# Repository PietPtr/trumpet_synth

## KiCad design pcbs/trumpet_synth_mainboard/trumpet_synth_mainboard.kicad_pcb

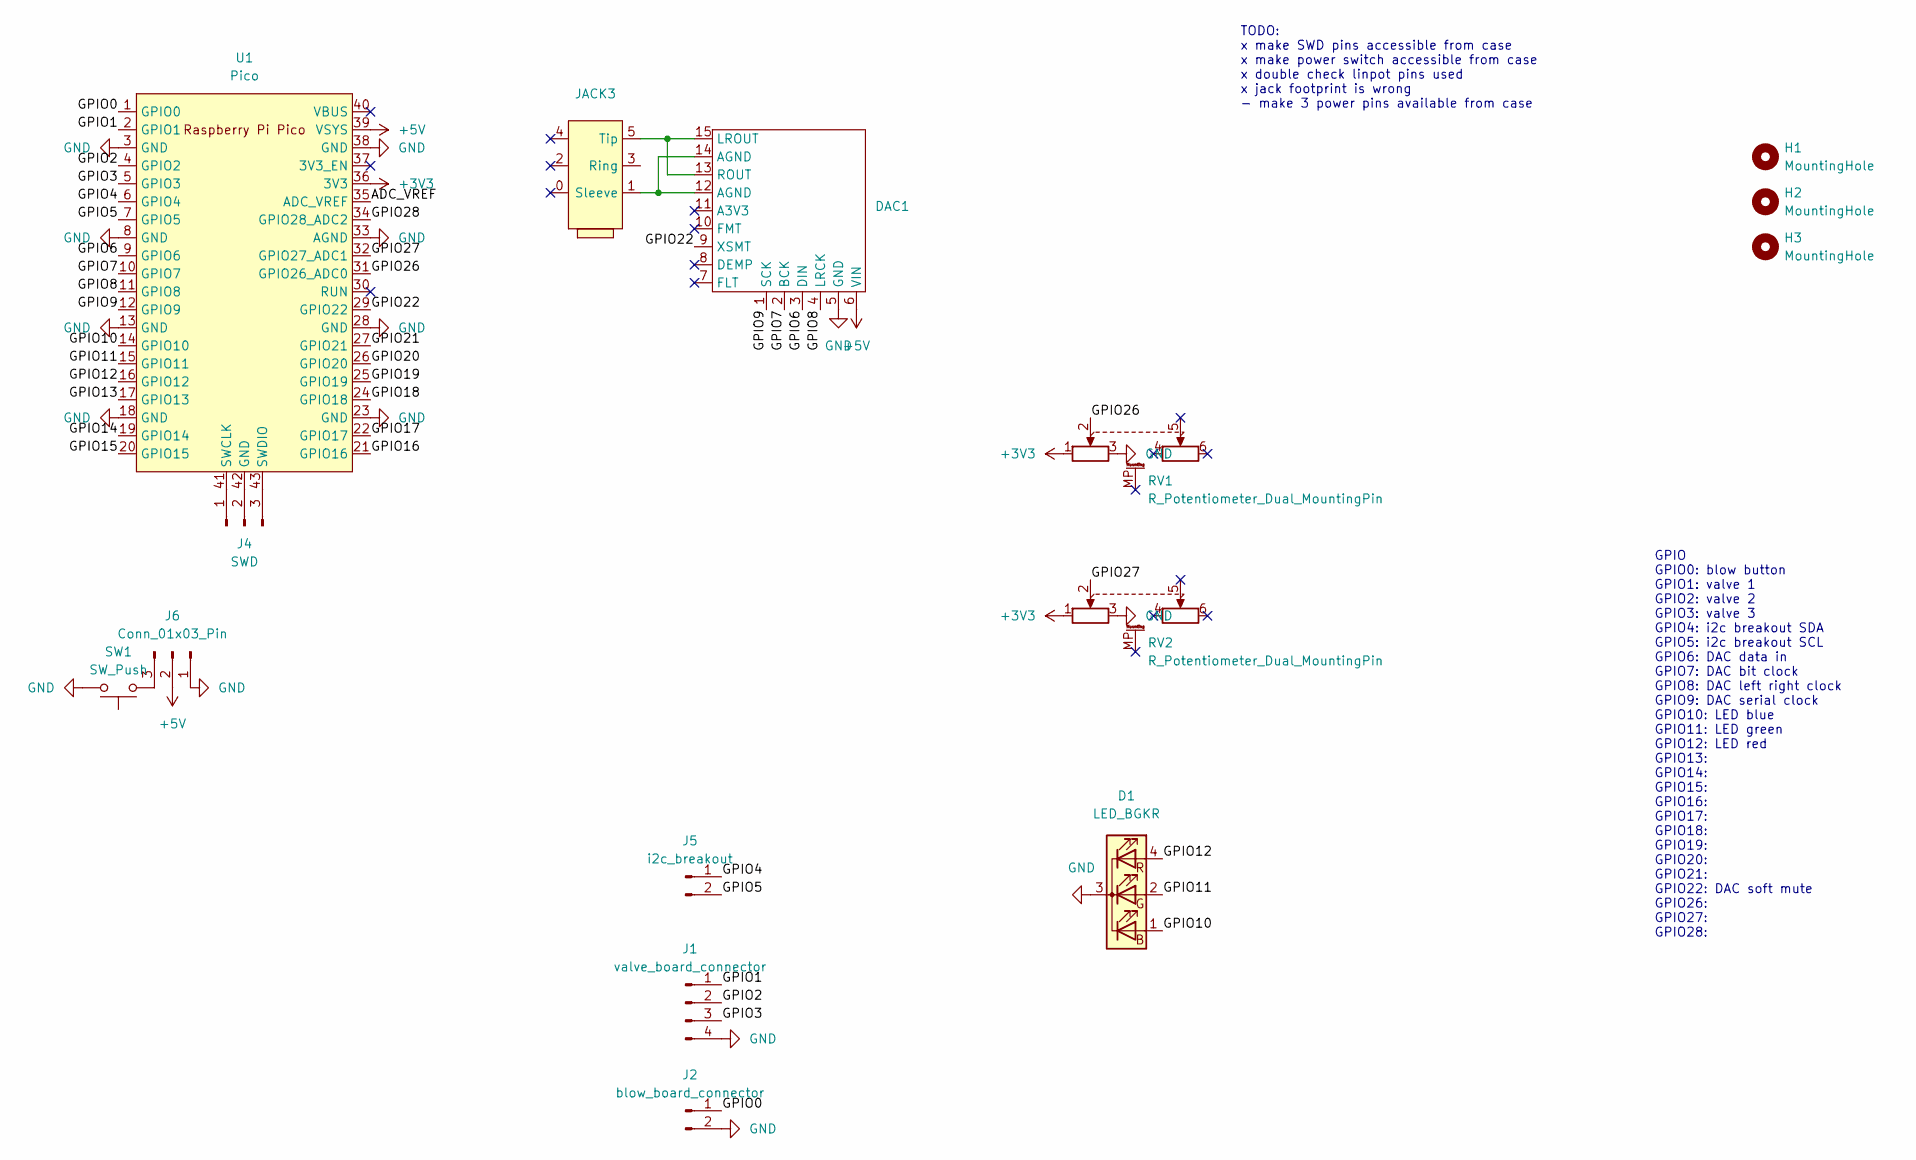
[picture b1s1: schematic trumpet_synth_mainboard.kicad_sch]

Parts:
D1: LED_BGKR; LED_D5.0mm-4_RGB
DAC1: PCM5102_BREAKOUT
H1, H2, H3: MountingHole; MountingHole_3.2mm_M3
J1: valve_board_connector; PinHeader_1x04_P2.54mm_Vertical
J2: blow_board_connector; PinHeader_1x02_P2.54mm_Vertical
J4: SWD; PinHeader_1x03_P2.54mm_Vertical
J5: i2c_breakout; PinHeader_1x02_P2.54mm_Vertical
J6: Conn_01x03_Pin; PinHeader_1x03_P2.54mm_Vertical
JACK3: SlimJack6.3
RV1, RV2: R_Potentiometer_Dual_MountingPin; linpot_75mm
SW1: SW_Push; PinHeader_1x03_P2.54mm_Vertical
U1: Pico; RPi_Pico_SMD

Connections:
+3V3: RV1.1, RV2.1, U1.36 (3V3)
+5V: DAC1.6 (VIN), J6.2, U1.39 (VSYS)
/ADC_VREF: U1.35 (ADC_VREF)
/GPIO0: J2.1, U1.1 (GPIO0)
/GPIO1: J1.1, U1.2 (GPIO1)
/GPIO2: J1.2, U1.4 (GPIO2)
/GPIO3: J1.3, U1.5 (GPIO3)
/GPIO4: J5.1, U1.6 (GPIO4)
/GPIO5: J5.2, U1.7 (GPIO5)
/GPIO6: DAC1.3 (DIN), U1.9 (GPIO6)
/GPIO7: DAC1.2 (BCK), U1.10 (GPIO7)
/GPIO8: DAC1.4 (LRCK), U1.11 (GPIO8)
/GPIO9: DAC1.1 (SCK), U1.12 (GPIO9)
/GPIO10: D1.1 (BA), U1.14 (GPIO10)
/GPIO11: D1.2 (GA), U1.15 (GPIO11)
/GPIO12: D1.4 (RA), U1.16 (GPIO12)
/GPIO13: U1.17 (GPIO13)
/GPIO14: U1.19 (GPIO14)
/GPIO15: U1.20 (GPIO15)
/GPIO16: U1.21 (GPIO16)
/GPIO17: U1.22 (GPIO17)
/GPIO18: U1.24 (GPIO18)
/GPIO19: U1.25 (GPIO19)
/GPIO20: U1.26 (GPIO20)
/GPIO21: U1.27 (GPIO21)
/GPIO22: DAC1.9 (XSMT), U1.29 (GPIO22)
/GPIO26: RV1.2, U1.31 (GPIO26_ADC0)
/GPIO27: RV2.2, U1.32 (GPIO27_ADC1)
/GPIO28: U1.34 (GPIO28_ADC2)
GND: D1.3 (K), DAC1.5 (GND), J1.4, J2.2, J6.1, RV1.3, RV2.3, SW1.2, U1.3 (GND), U1.8 (GND), U1.13 (GND), U1.18 (GND), U1.23 (GND), U1.28 (GND), U1.33 (AGND), U1.38 (GND)
unnamed: DAC1.13 (ROUT), DAC1.15 (LROUT), JACK3.5 (Tip)
unnamed: J4.1, U1.41 (SWCLK)
unnamed: J4.2, U1.42 (GND)
unnamed: J4.3, U1.43 (SWDIO)
unnamed: J6.3, SW1.1
unnamed: DAC1.12 (AGND), DAC1.14 (AGND), JACK3.1 (Sleeve)

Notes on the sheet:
TODO: x make SWD pins accessible from case x make power switch accessible from case x double check linpot pins used x jack footprint is wrong - make 3 power pins available from case
GPIO GPIO0: blow button GPIO1: valve 1 GPIO2: valve 2 GPIO3: valve 3 GPIO4: i2c breakout SDA GPIO5: i2c breakout SCL GPIO6: DAC data in GPIO7: DAC bit clock GPIO8: DAC left right clock GPIO9: DAC serial clock GPIO10: LED blue GPIO11: LED green GPIO12: LED red GPIO13: GPIO14: GPIO15: GPIO16: GPIO17: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

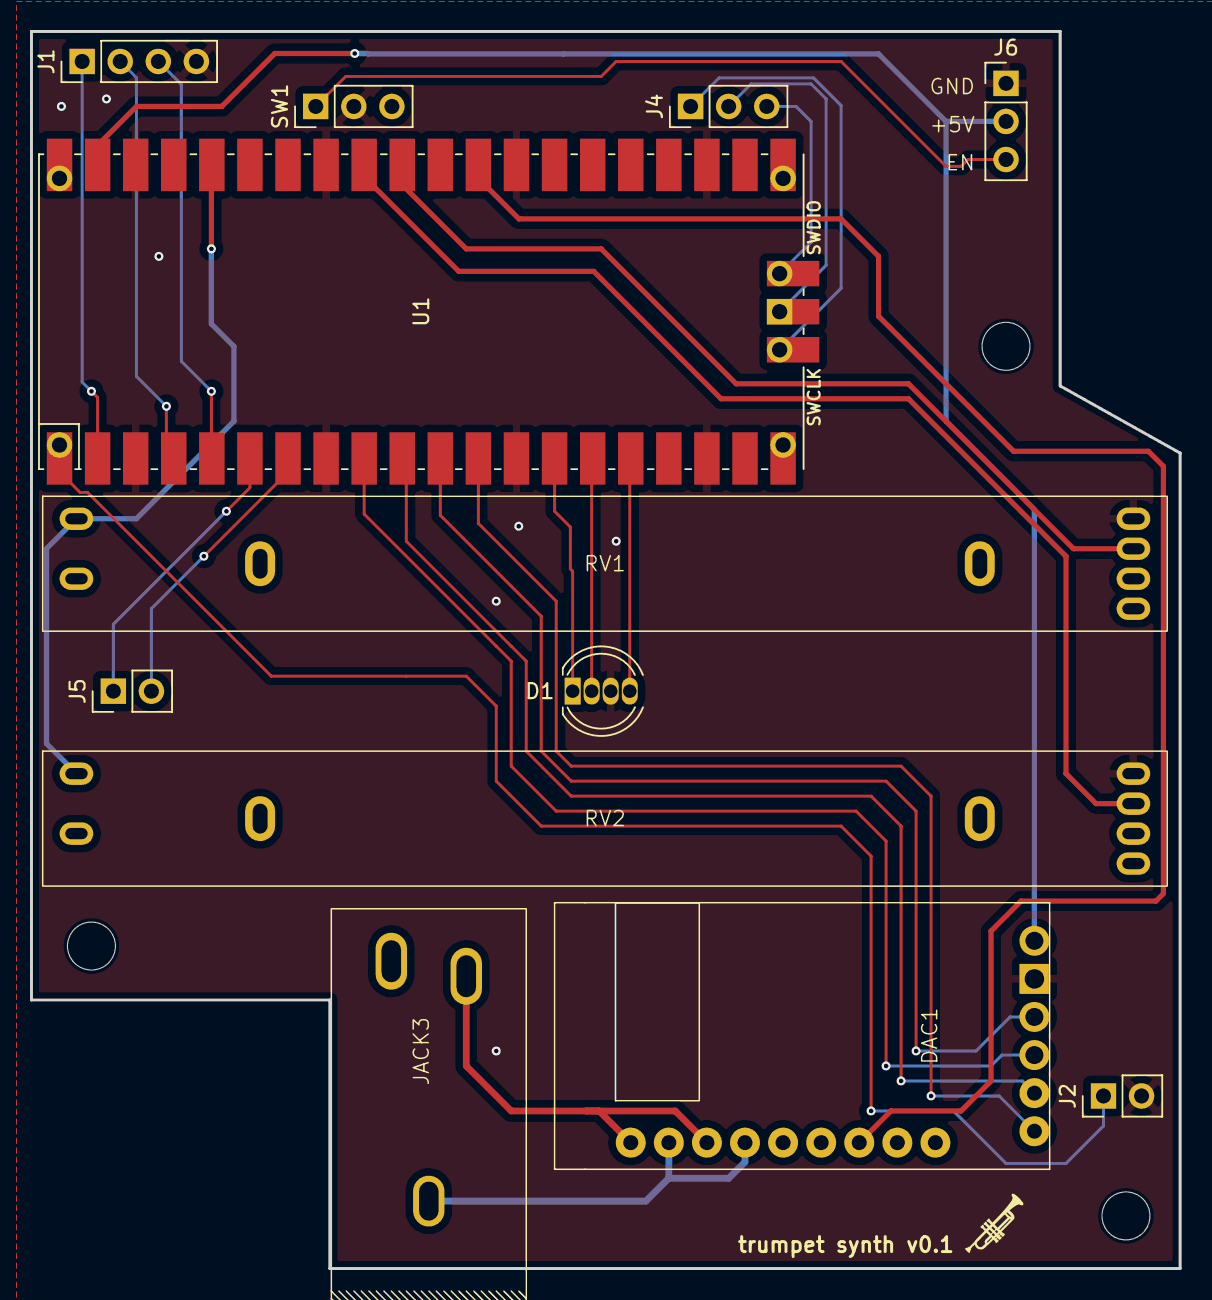
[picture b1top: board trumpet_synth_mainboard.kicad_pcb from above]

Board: 2 copper layers, 76.6 x 82.5 mm, 15 parts (0 on the bottom side), 25 nets.

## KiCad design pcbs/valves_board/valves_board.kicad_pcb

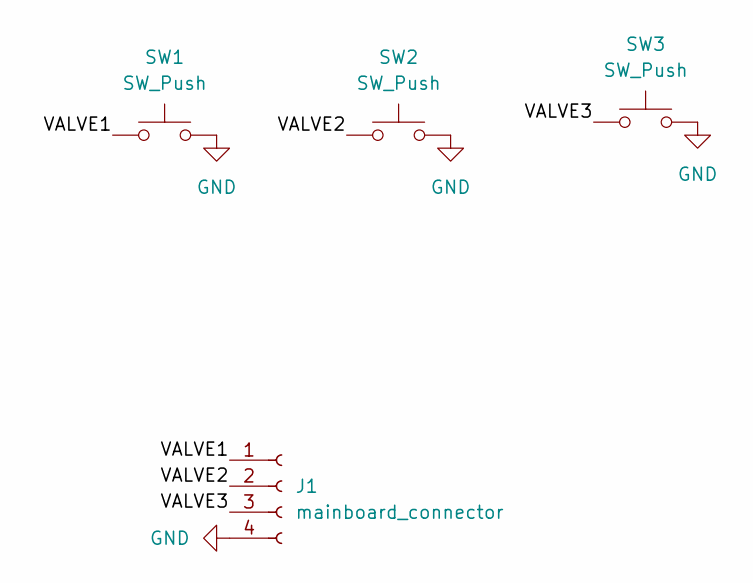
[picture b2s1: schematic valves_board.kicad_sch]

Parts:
J1: mainboard_connector; PinSocket_1x04_P2.54mm_Vertical
SW1, SW2, SW3: SW_Push; SW_Cherry_MX_1.00u_PCB

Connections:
/VALVE1: J1.1, SW1.1
/VALVE2: J1.2, SW2.1
/VALVE3: J1.3, SW3.1
GND: J1.4, SW1.2, SW2.2, SW3.2

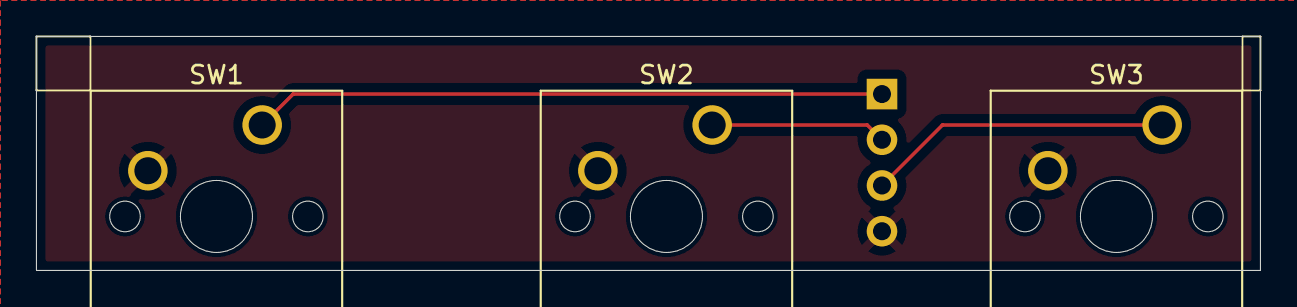
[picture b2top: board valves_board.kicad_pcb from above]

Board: 2 copper layers, 68.0 x 13.0 mm, 4 parts (1 on the bottom side), 4 nets.

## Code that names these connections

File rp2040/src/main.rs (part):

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use panic_probe as _;
use pio_proc::pio_file;
use rgb::TrumpetRgbLed;
use rp2040_hal::gpio::bank0::Gpio0;
use rp2040_hal::gpio::{DynFunction, DynPinId, FunctionSioInput, Pin, PullDown};
use rp2040_hal::pac;
use rp2040_hal::{
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    entry,
    gpio::{
        self,
        bank0::{Gpio10, Gpio11, Gpio12},
        FunctionPio0, FunctionPwm, PullUp,
    },
    multicore::{Multicore, Stack},
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
    // -- move to lib --

    let sck_pin: gpio::Pin<gpio::bank0::Gpio9, gpio::FunctionPio0, gpio::PullDown> =
        pins.gpio9.reconfigure();
    {
        #[rustfmt::skip]
        let sck_pio_program = pio_proc::pio_asm!(
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        &mut pio0,
        rp2040_i2s::PioClockDivider::FromSystemClock(sys_freq),
        sm0,
        pins.gpio6,
        pins.gpio7,
        pins.gpio8,
    )
    .unwrap();

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    );
    let mut delay = cortex_m::delay::Delay::new(core.SYST, sys_freq);

    let i2s_sck_pin = pins.gpio9.into_function::<FunctionPio0>();
    let i2s_din_pin = pins.gpio6.into_function::<FunctionPio0>();
    let i2s_bck_pin = pins.gpio7.into_function::<FunctionPio0>();
    let i2s_lck_pin = pins.gpio8.into_function::<FunctionPio0>();

    let pio_i2s_mclk_output = pio_file!("src/i2s.pio", select_program("mclk_output")).program;
    let pio_i2s_send_master = pio_file!("src/i2s.pio", select_program("i2s_out_master")).program;
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    );

    let valve_pins = [
        pins.gpio1.into_pull_up_input().into_dyn_pin(),
        pins.gpio16.into_pull_up_input().into_dyn_pin(), // Should be 2, is patched on the test PCB
        pins.gpio3.into_pull_up_input().into_dyn_pin(),
    ];

    let blow_pin: gpio::Pin<Gpio0, FunctionSioInput, PullUp> = pins.gpio0.reconfigure();

    let adc_pins: [AdcPin<Pin<DynPinId, DynFunction, PullDown>>; 2] = [
        AdcPin::new(pins.gpio26.reconfigure().into_dyn_pin()).unwrap(),
        AdcPin::new(pins.gpio27.reconfigure().into_dyn_pin()).unwrap(),
    ];

    let adc = Adc::new(pac.ADC, &mut pac.RESETS);

    let r: gpio::Pin<Gpio10, FunctionPwm, PullUp> = pins.gpio10.reconfigure();
    let g: gpio::Pin<Gpio11, FunctionPwm, PullUp> = pins.gpio11.reconfigure();
    let b: gpio::Pin<Gpio12, FunctionPwm, PullUp> = pins.gpio12.reconfigure();

    let pwm_slices = pwm::Slices::new(pac.PWM, &mut pac.RESETS);
    let mut pwm5 = pwm_slices.pwm5;
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
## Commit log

2025-05-20 Research trumpet definition
2025-05-27 Create button logic
2025-05-27 Work on interface
2025-05-28 Add basic frequency calculation
2025-05-28 Finish plumbing
2025-10-10 Add things like months ago
2025-10-10 Working sound synthesis with basic trumpet model
2025-10-12 Working rp2040 frontend, design pcbs
2025-10-13 Update PCBs
2025-10-15 Order all PCBs v0.1
2025-10-31 Add trumpet tester
2025-10-31 Tests on PCB
2025-10-31 Add vecdequeues
2025-10-31 Working tester to wav
2025-11-04 Add test case to emit to wav
2025-11-11 Add bends
2025-11-16 Refactor the synth used by the trumpet to make it easier to do something creative with later
